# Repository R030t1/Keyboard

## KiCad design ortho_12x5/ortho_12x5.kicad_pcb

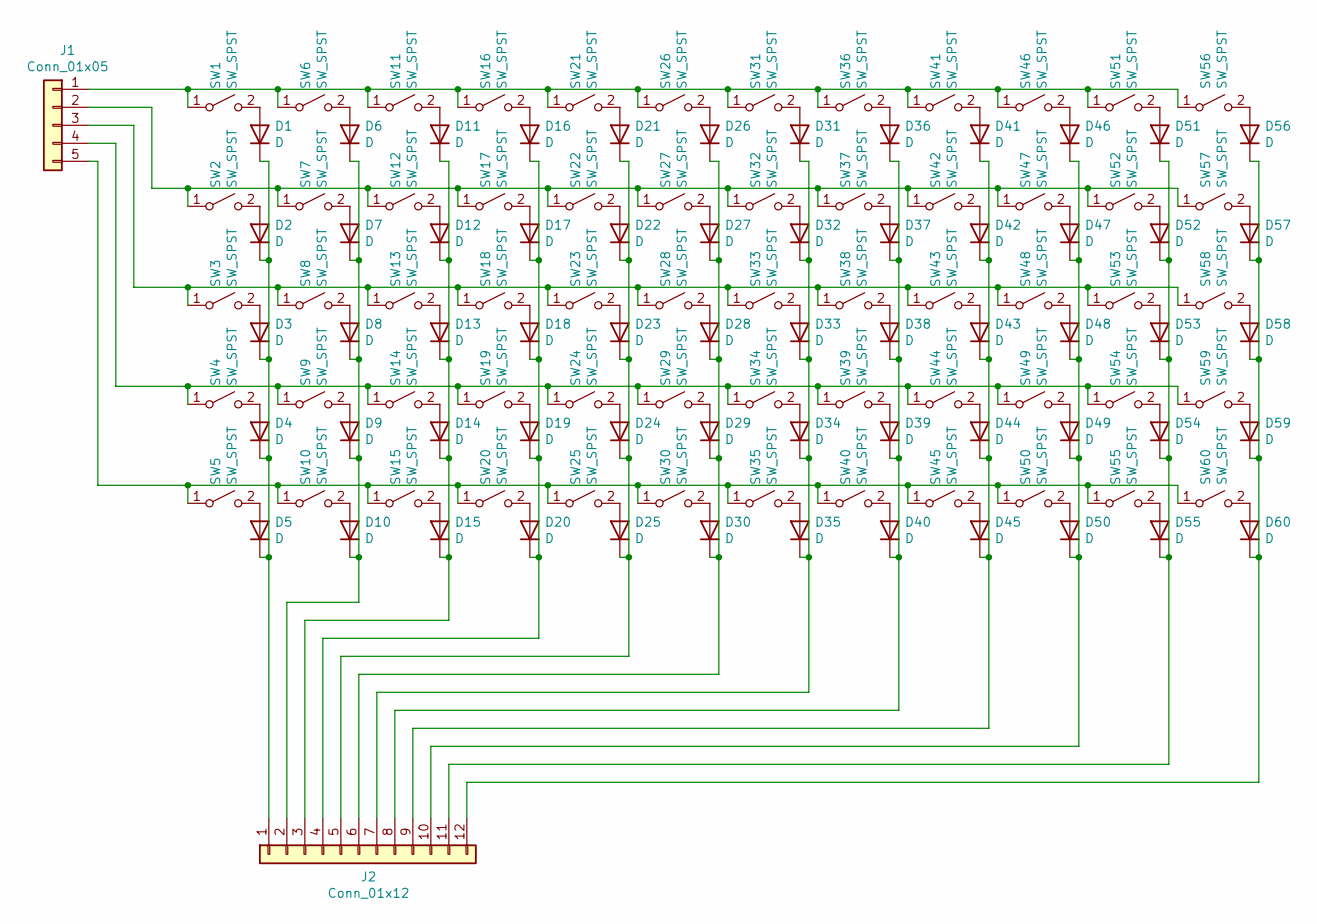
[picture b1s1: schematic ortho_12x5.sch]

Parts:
D1, D2, D3, D4, D5, D6, D7, D8, D9, D10, D11, D12, D13, D14, D15, D16, D17, D18, D19, D20, D21, D22, D23, D24, D25, D26, D27, D28, D29, D30, D31, D32, D33, D34, D35, D36, D37, D38, D39, D40, D41, D42, D43, D44, D45, D46, D47, D48, D49, D50, D51, D52, D53, D54, D55, D56, D57, D58, D59, D60: D; D_DO-34_SOD68_P7.62mm_Horizontal
J1: Conn_01x05; PinSocket_1x05_P2.54mm_Horizontal
J2: Conn_01x12; PinHeader_1x12_P2.54mm_Horizontal
SW1, SW2, SW3, SW4, SW5, SW6, SW7, SW8, SW9, SW10, SW11, SW12, SW13, SW14, SW15, SW16, SW17, SW18, SW19, SW20, SW21, SW22, SW23, SW24, SW25, SW26, SW27, SW28, SW29, SW30, SW31, SW32, SW33, SW34, SW35, SW36, SW37, SW38, SW39, SW40, SW41, SW42, SW43, SW44, SW45, SW46, SW47, SW48, SW49, SW50, SW51, SW52, SW53, SW54, SW55, SW56, SW57, SW58, SW59, SW60: SW_SPST; SW_Cherry_MX_1.00u_PCB

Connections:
unnamed: D1.1 (K), D2.1 (K), D3.1 (K), D4.1 (K), D5.1 (K), J2.1
unnamed: D1.2 (A), SW1.2 (B)
unnamed: D2.2 (A), SW2.2 (B)
unnamed: D3.2 (A), SW3.2 (B)
unnamed: D4.2 (A), SW4.2 (B)
unnamed: D5.2 (A), SW5.2 (B)
unnamed: D6.2 (A), SW6.2 (B)
unnamed: D7.2 (A), SW7.2 (B)
unnamed: D8.2 (A), SW8.2 (B)
unnamed: D9.2 (A), SW9.2 (B)
unnamed: D6.1 (K), D7.1 (K), D8.1 (K), D9.1 (K), D10.1 (K), J2.2
unnamed: D10.2 (A), SW10.2 (B)
unnamed: D11.1 (K), D12.1 (K), D13.1 (K), D14.1 (K), D15.1 (K), J2.3
unnamed: D11.2 (A), SW11.2 (B)
unnamed: D12.2 (A), SW12.2 (B)
unnamed: D13.2 (A), SW13.2 (B)
unnamed: D14.2 (A), SW14.2 (B)
unnamed: D15.2 (A), SW15.2 (B)
unnamed: D16.1 (K), D17.1 (K), D18.1 (K), D19.1 (K), D20.1 (K), J2.4
unnamed: D16.2 (A), SW16.2 (B)
unnamed: D17.2 (A), SW17.2 (B)
unnamed: D18.2 (A), SW18.2 (B)
unnamed: D19.2 (A), SW19.2 (B)
unnamed: D20.2 (A), SW20.2 (B)
unnamed: D21.1 (K), D22.1 (K), D23.1 (K), D24.1 (K), D25.1 (K), J2.5
unnamed: D21.2 (A), SW21.2 (B)
unnamed: D22.2 (A), SW22.2 (B)
unnamed: D23.2 (A), SW23.2 (B)
unnamed: D24.2 (A), SW24.2 (B)
unnamed: D25.2 (A), SW25.2 (B)
unnamed: D26.1 (K), D27.1 (K), D28.1 (K), D29.1 (K), D30.1 (K), J2.6
unnamed: D26.2 (A), SW26.2 (B)
unnamed: D27.2 (A), SW27.2 (B)
unnamed: D28.2 (A), SW28.2 (B)
unnamed: D29.2 (A), SW29.2 (B)
unnamed: D30.2 (A), SW30.2 (B)
unnamed: D31.1 (K), D32.1 (K), D33.1 (K), D34.1 (K), D35.1 (K), J2.7
unnamed: D31.2 (A), SW31.2 (B)
unnamed: D32.2 (A), SW32.2 (B)
unnamed: D33.2 (A), SW33.2 (B)
unnamed: D34.2 (A), SW34.2 (B)
unnamed: D35.2 (A), SW35.2 (B)
unnamed: D36.1 (K), D37.1 (K), D38.1 (K), D39.1 (K), D40.1 (K), J2.8
unnamed: D36.2 (A), SW36.2 (B)
unnamed: D37.2 (A), SW37.2 (B)
unnamed: D38.2 (A), SW38.2 (B)
unnamed: D39.2 (A), SW39.2 (B)
unnamed: D40.2 (A), SW40.2 (B)
unnamed: D41.1 (K), D42.1 (K), D43.1 (K), D44.1 (K), D45.1 (K), J2.9
unnamed: D41.2 (A), SW41.2 (B)
unnamed: D42.2 (A), SW42.2 (B)
unnamed: D43.2 (A), SW43.2 (B)
unnamed: D44.2 (A), SW44.2 (B)
unnamed: D45.2 (A), SW45.2 (B)
unnamed: D46.1 (K), D47.1 (K), D48.1 (K), D49.1 (K), D50.1 (K), J2.10
unnamed: D46.2 (A), SW46.2 (B)
unnamed: D47.2 (A), SW47.2 (B)
unnamed: D48.2 (A), SW48.2 (B)
unnamed: D49.2 (A), SW49.2 (B)
unnamed: D50.2 (A), SW50.2 (B)
unnamed: D51.1 (K), D52.1 (K), D53.1 (K), D54.1 (K), D55.1 (K), J2.11
unnamed: D51.2 (A), SW51.2 (B)
unnamed: D52.2 (A), SW52.2 (B)
unnamed: D53.2 (A), SW53.2 (B)
unnamed: D54.2 (A), SW54.2 (B)
unnamed: D55.2 (A), SW55.2 (B)
unnamed: D56.1 (K), D57.1 (K), D58.1 (K), D59.1 (K), D60.1 (K), J2.12
unnamed: D56.2 (A), SW56.2 (B)
unnamed: D57.2 (A), SW57.2 (B)
unnamed: D58.2 (A), SW58.2 (B)
unnamed: D59.2 (A), SW59.2 (B)
unnamed: D60.2 (A), SW60.2 (B)
unnamed: J1.1, SW1.1 (A), SW6.1 (A), SW11.1 (A), SW16.1 (A), SW21.1 (A), SW26.1 (A), SW31.1 (A), SW36.1 (A), SW41.1 (A), SW46.1 (A), SW51.1 (A), SW56.1 (A)
unnamed: J1.2, SW2.1 (A), SW7.1 (A), SW12.1 (A), SW17.1 (A), SW22.1 (A), SW27.1 (A), SW32.1 (A), SW37.1 (A), SW42.1 (A), SW47.1 (A), SW52.1 (A), SW57.1 (A)
unnamed: J1.3, SW3.1 (A), SW8.1 (A), SW13.1 (A), SW18.1 (A), SW23.1 (A), SW28.1 (A), SW33.1 (A), SW38.1 (A), SW43.1 (A), SW48.1 (A), SW53.1 (A), SW58.1 (A)
unnamed: J1.4, SW4.1 (A), SW9.1 (A), SW14.1 (A), SW19.1 (A), SW24.1 (A), SW29.1 (A), SW34.1 (A), SW39.1 (A), SW44.1 (A), SW49.1 (A), SW54.1 (A), SW59.1 (A)
unnamed: J1.5, SW5.1 (A), SW10.1 (A), SW15.1 (A), SW20.1 (A), SW25.1 (A), SW30.1 (A), SW35.1 (A), SW40.1 (A), SW45.1 (A), SW50.1 (A), SW55.1 (A), SW60.1 (A)

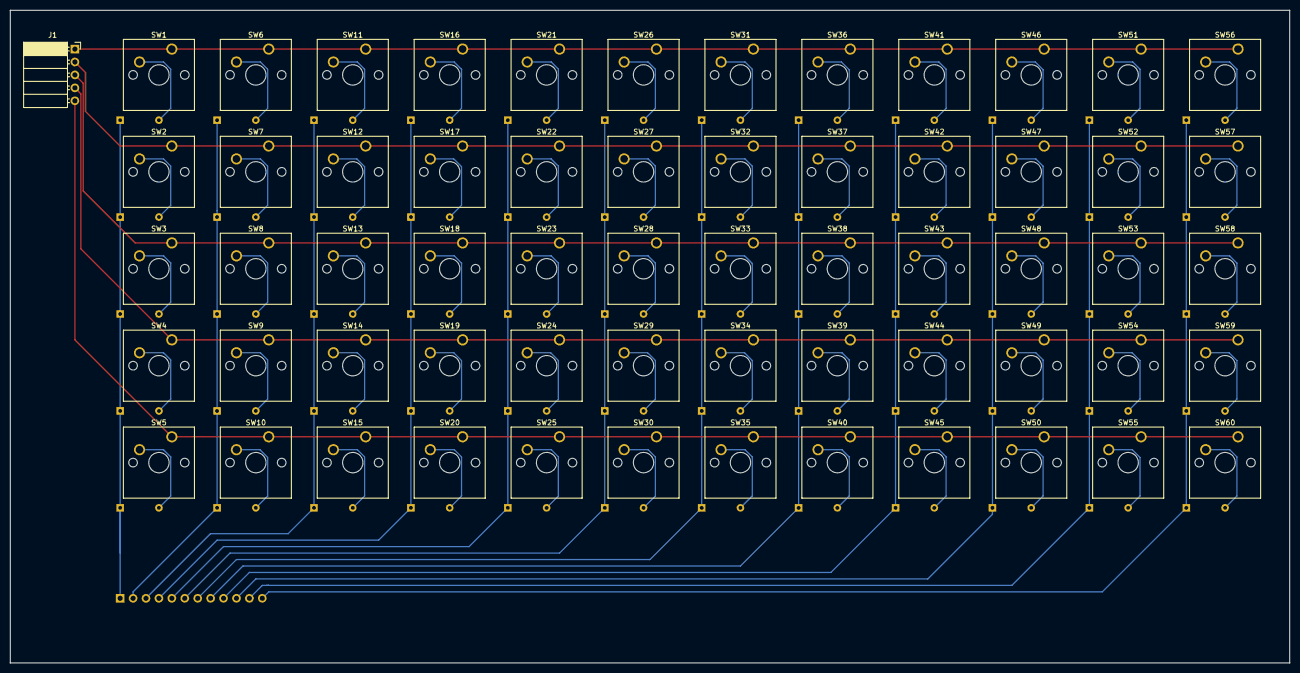
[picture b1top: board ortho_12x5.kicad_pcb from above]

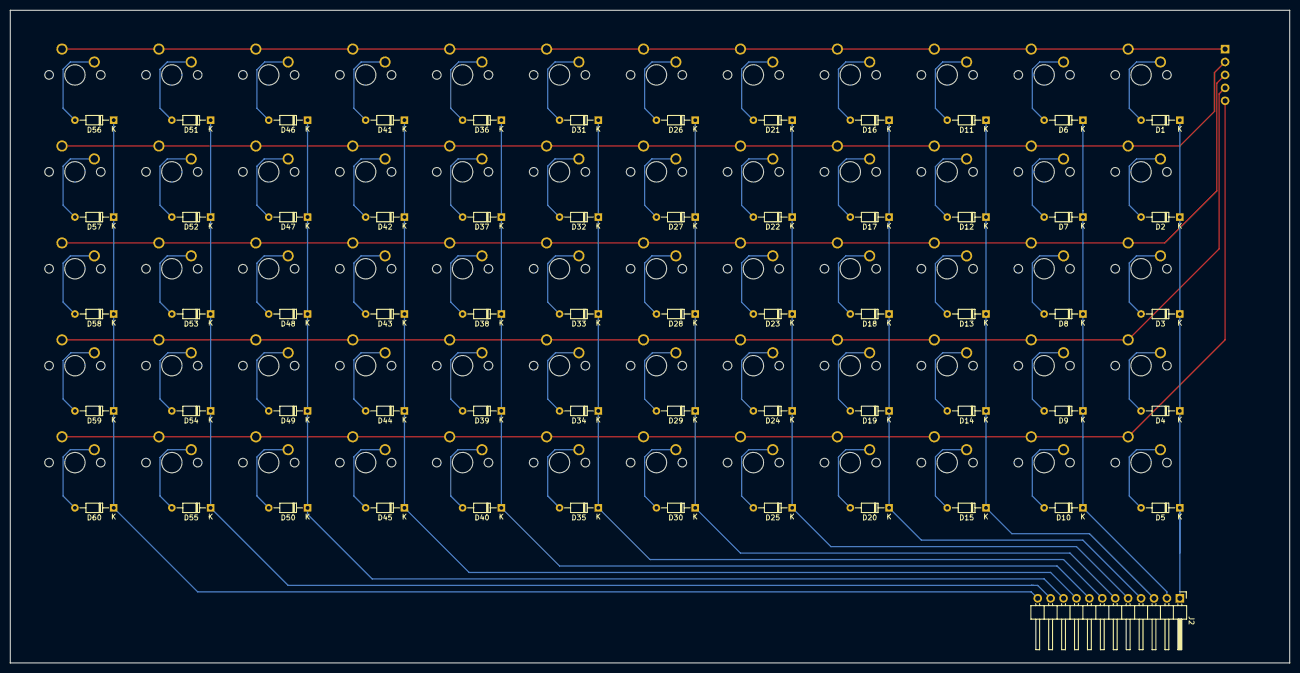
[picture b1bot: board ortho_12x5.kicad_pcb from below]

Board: 2 copper layers, 251.5 x 128.3 mm, 122 parts (61 on the bottom side), 77 nets.

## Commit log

2021-01-06 Add main grid to schematic
2021-01-09 Start layout
2021-01-11 Redo schematic
2021-01-12 Clean up, need to get switch clearances
2021-01-14 Fix schematic, place components; need route
2021-01-15 Fully routed, need to check layout
2021-01-18 Add generated gerbers
2021-01-18 Add drill files
2021-03-04 Start new
